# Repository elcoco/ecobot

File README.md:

# Ecobot :: A robot that draws stuff

Included in the repo are:

- CAD files created with [Freecad](https://www.freecadweb.org).
- PCB files created with [Kicad](https://www.kicad.org/).

Projects used:

- The [ESP32 port](https://github.com/bdring/Grbl_Esp32) of the great [GRBL](https://github.com/gnea/grbl) CNC controller firmware.
- [BCNC](https://github.com/vlachoudis/bCNC) command sender, autoleveler, g-code editor, digitizer, CAM and swiss army knife for all your CNC needs.

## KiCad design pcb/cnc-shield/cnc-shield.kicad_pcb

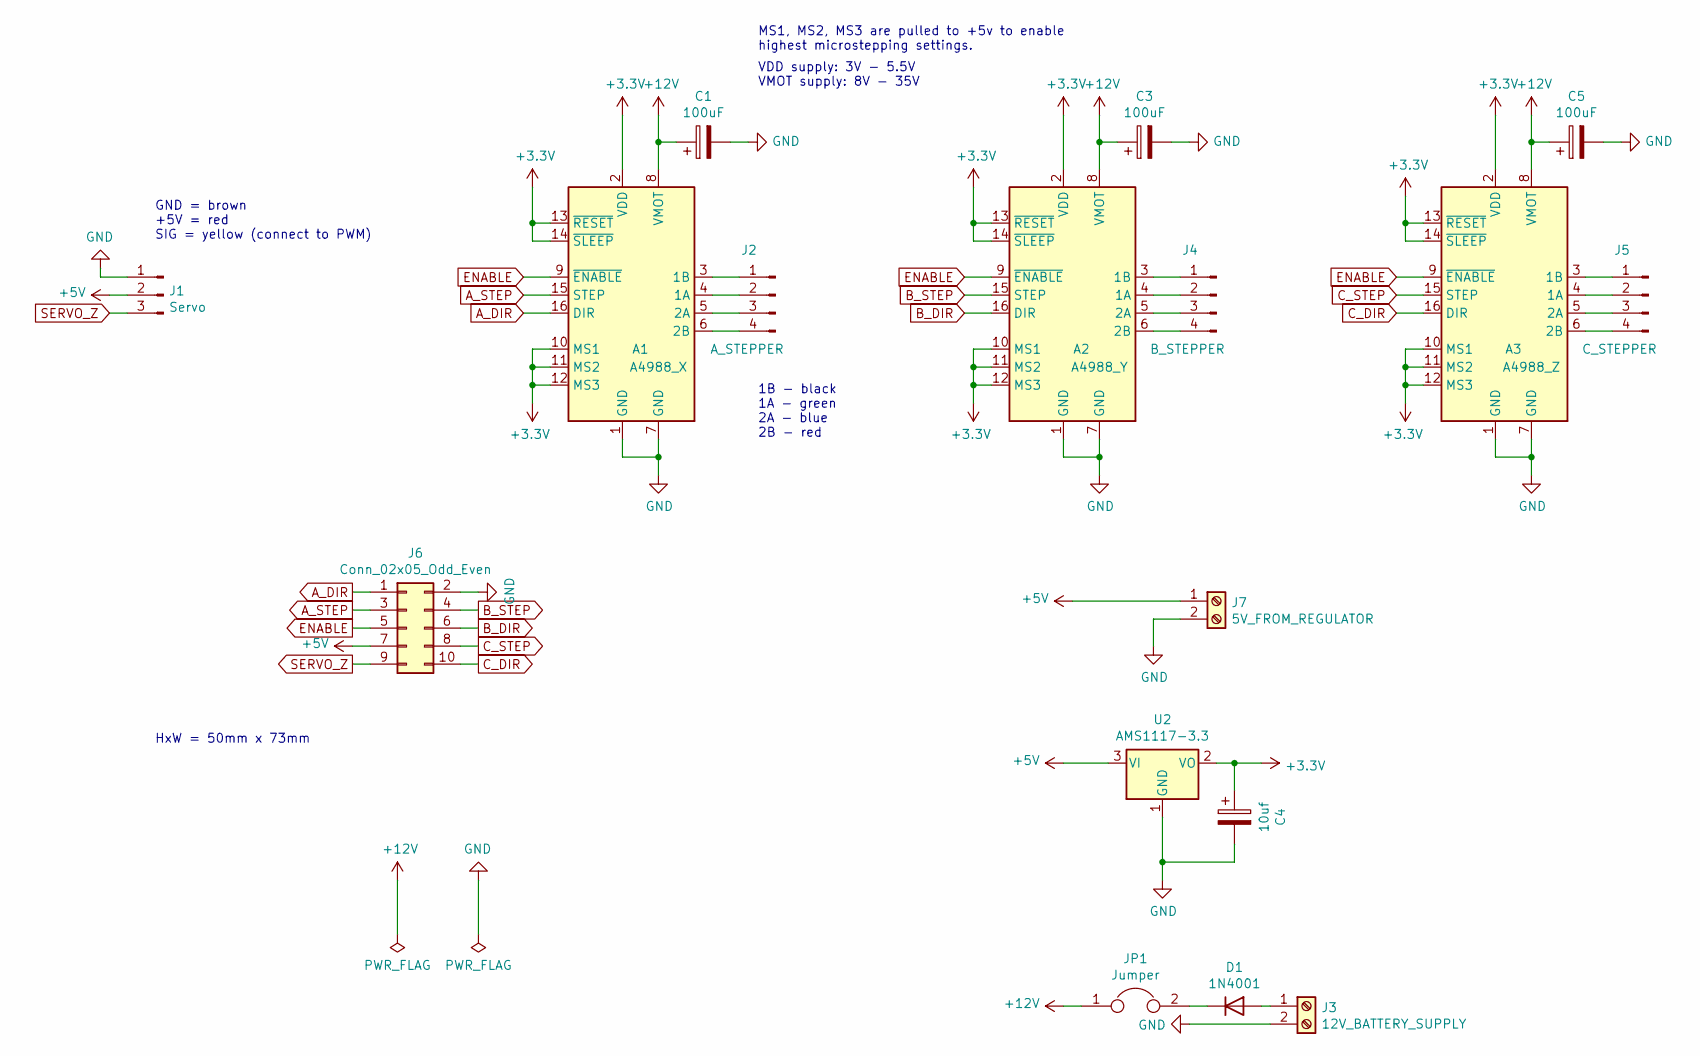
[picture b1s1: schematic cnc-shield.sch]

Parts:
A1: A4988_X; Pololu_Breakout-16_15.2x20.3mm
A2: A4988_Y; Pololu_Breakout-16_15.2x20.3mm
A3: A4988_Z; Pololu_Breakout-16_15.2x20.3mm
C1, C3, C5: 100uF; CP_Radial_D8.0mm_P3.80mm
C4: 10uf; CP_Radial_D8.0mm_P3.80mm
D1: 1N4001; D_DO-41_SOD81_P10.16mm_Horizontal
J1: Servo; PinHeader_1x03_P2.54mm_Vertical
J2: A_STEPPER; PinHeader_1x04_P2.54mm_Vertical
J3: 12V_BATTERY_SUPPLY; TerminalBlock_Phoenix_MKDS-1,5-2-5.08_1x02_P5.08mm_Horizont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
J4: B_STEPPER; PinHeader_1x04_P2.54mm_Vertical
J5: C_STEPPER; PinHeader_1x04_P2.54mm_Vertical
J6: Conn_02x05_Odd_Even; 2X5-SHROUDED_LOCK
J7: 5V_FROM_REGULATOR; TerminalBlock_Phoenix_MKDS-1,5-2-5.08_1x02_P5.08mm_Horizont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
JP1: Jumper; PinHeader_1x02_P2.54mm_Vertical
U2: AMS1117-3.3; SOT-223-3_TabPin2

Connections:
+3V3: A1.2 (VDD), A1.10 (MS1), A1.11 (MS2), A1.12 (MS3), A1.13 (~RESET), A1.14 (~SLEEP), A2.2 (VDD), A2.10 (MS1), A2.11 (MS2), A2.12 (MS3), A2.13 (~RESET), A2.14 (~SLEEP), A3.2 (VDD), A3.10 (MS1), A3.11 (MS2), A3.12 (MS3), A3.13 (~RESET), A3.14 (~SLEEP), C4.1, U2.2 (VO)
+5V: J1.2, J6.7, J7.1, U2.3 (VI)
+12V: A1.8 (VMOT), A2.8 (VMOT), A3.8 (VMOT), C1.1, C3.1, C5.1, JP1.1
A_DIR: A1.16 (DIR), J6.1
A_STEP: A1.15 (STEP), J6.3
B_DIR: A2.16 (DIR), J6.6
B_STEP: A2.15 (STEP), J6.4
C_DIR: A3.16 (DIR), J6.10
C_STEP: A3.15 (STEP), J6.8
ENABLE: A1.9 (~ENABLE), A2.9 (~ENABLE), A3.9 (~ENABLE), J6.5
GND: A1.1 (GND), A1.7 (GND), A2.1 (GND), A2.7 (GND), A3.1 (GND), A3.7 (GND), C1.2, C3.2, C4.2, C5.2, J1.1, J3.2, J6.2, J7.2, U2.1 (GND)
unnamed: A1.3 (1B), J2.1
unnamed: A1.4 (1A), J2.2
unnamed: A1.5 (2A), J2.3
unnamed: A1.6 (2B), J2.4
unnamed: A2.3 (1B), J4.1
unnamed: A2.4 (1A), J4.2
unnamed: A2.5 (2A), J4.3
unnamed: A2.6 (2B), J4.4
unnamed: A3.3 (1B), J5.1
unnamed: A3.4 (1A), J5.2
unnamed: A3.5 (2A), J5.3
unnamed: A3.6 (2B), J5.4
unnamed: D1.1 (K), JP1.2
unnamed: D1.2 (A), J3.1
SERVO_Z: J1.3, J6.9

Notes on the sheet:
MS1, MS2, MS3 are pulled to +5v to enable highest microstepping settings.
GND = brown +5V = red SIG = yellow (connect to PWM)
HxW = 50mm x 73mm
1B - black 1A - green 2A - blue 2B - red
VDD supply: 3V - 5.5V VMOT supply: 8V - 35V

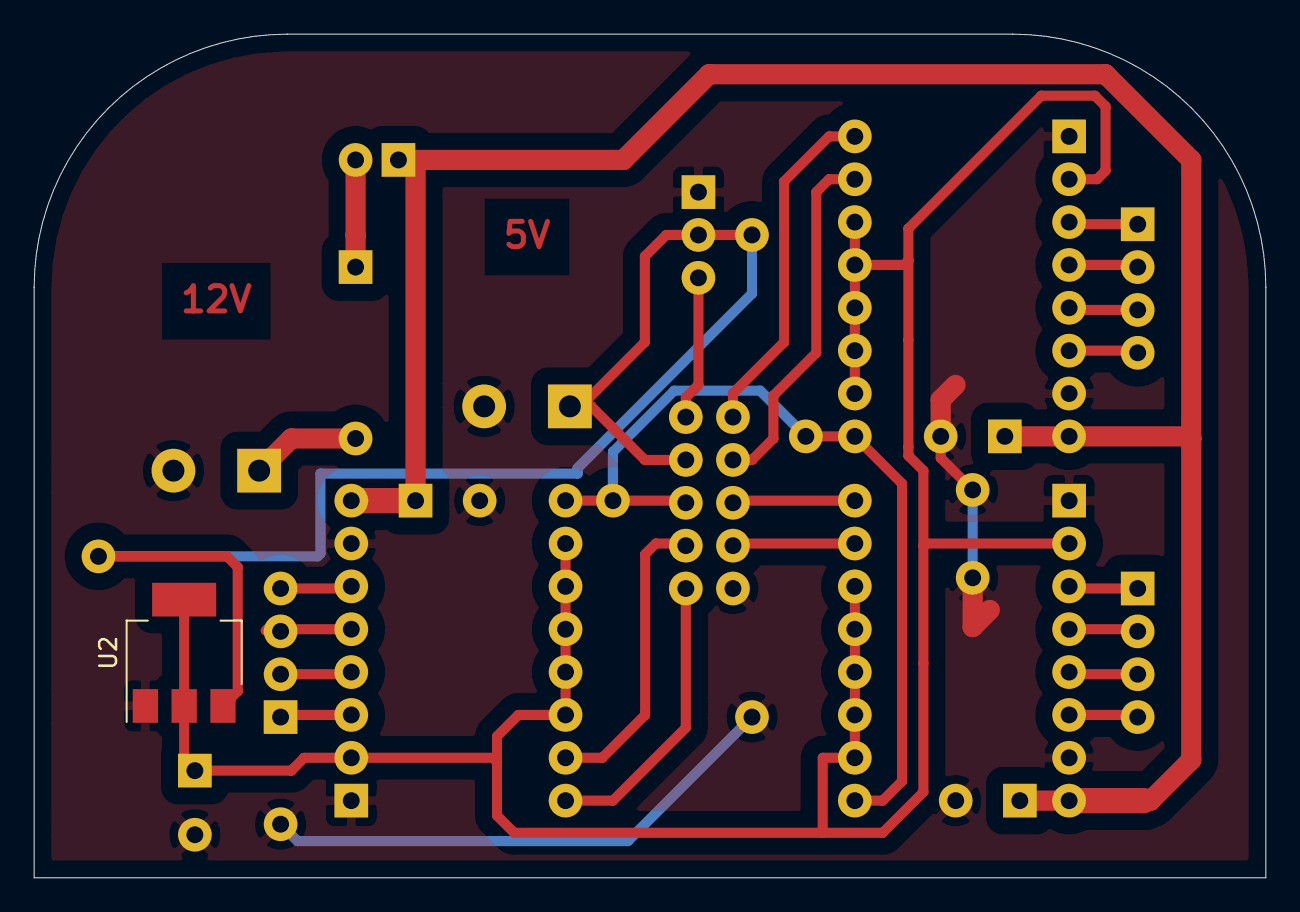
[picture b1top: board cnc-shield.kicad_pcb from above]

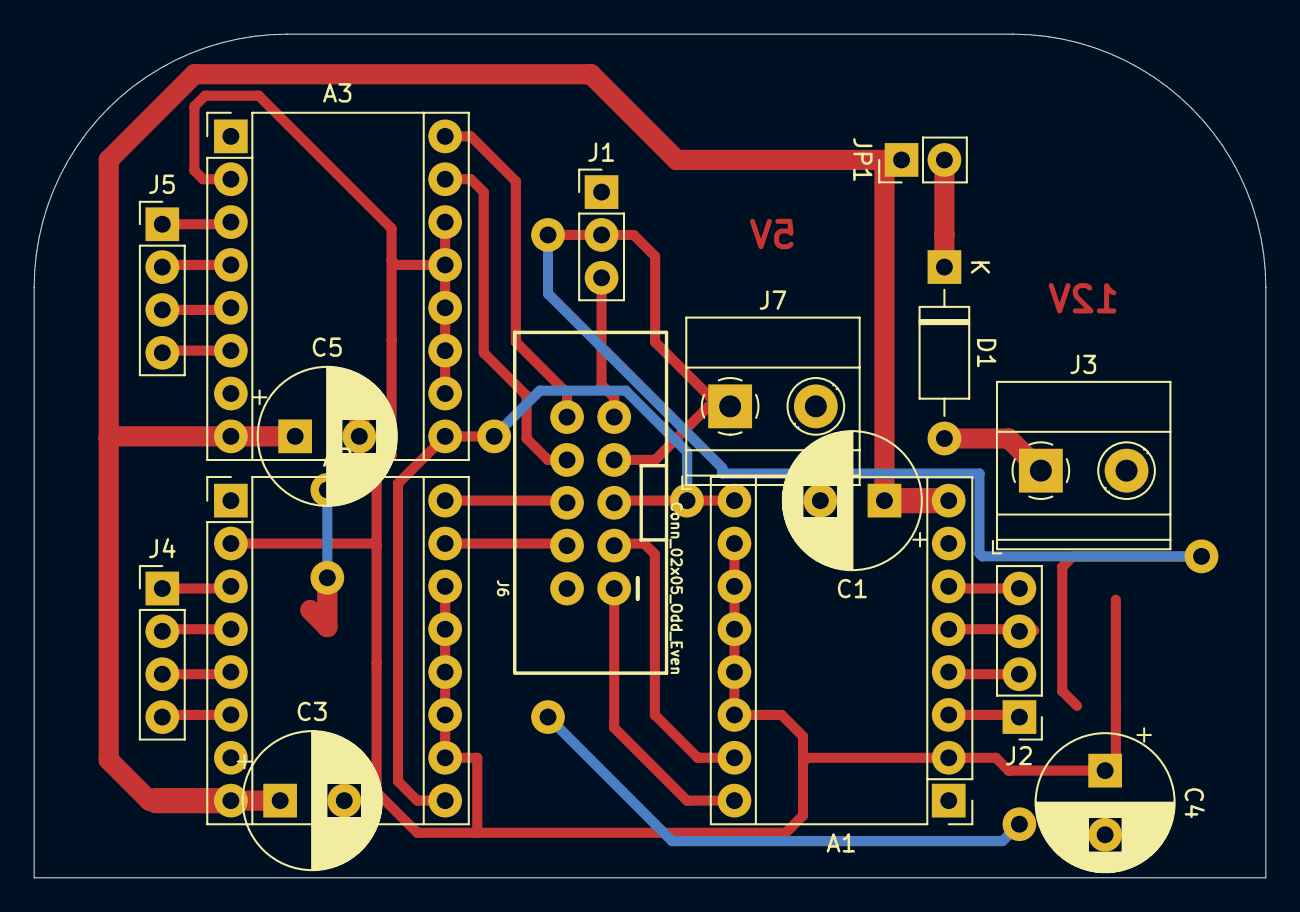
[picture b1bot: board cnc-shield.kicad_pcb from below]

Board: 2 copper layers, 73.0 x 50.0 mm, 17 parts (16 on the bottom side), 26 nets.

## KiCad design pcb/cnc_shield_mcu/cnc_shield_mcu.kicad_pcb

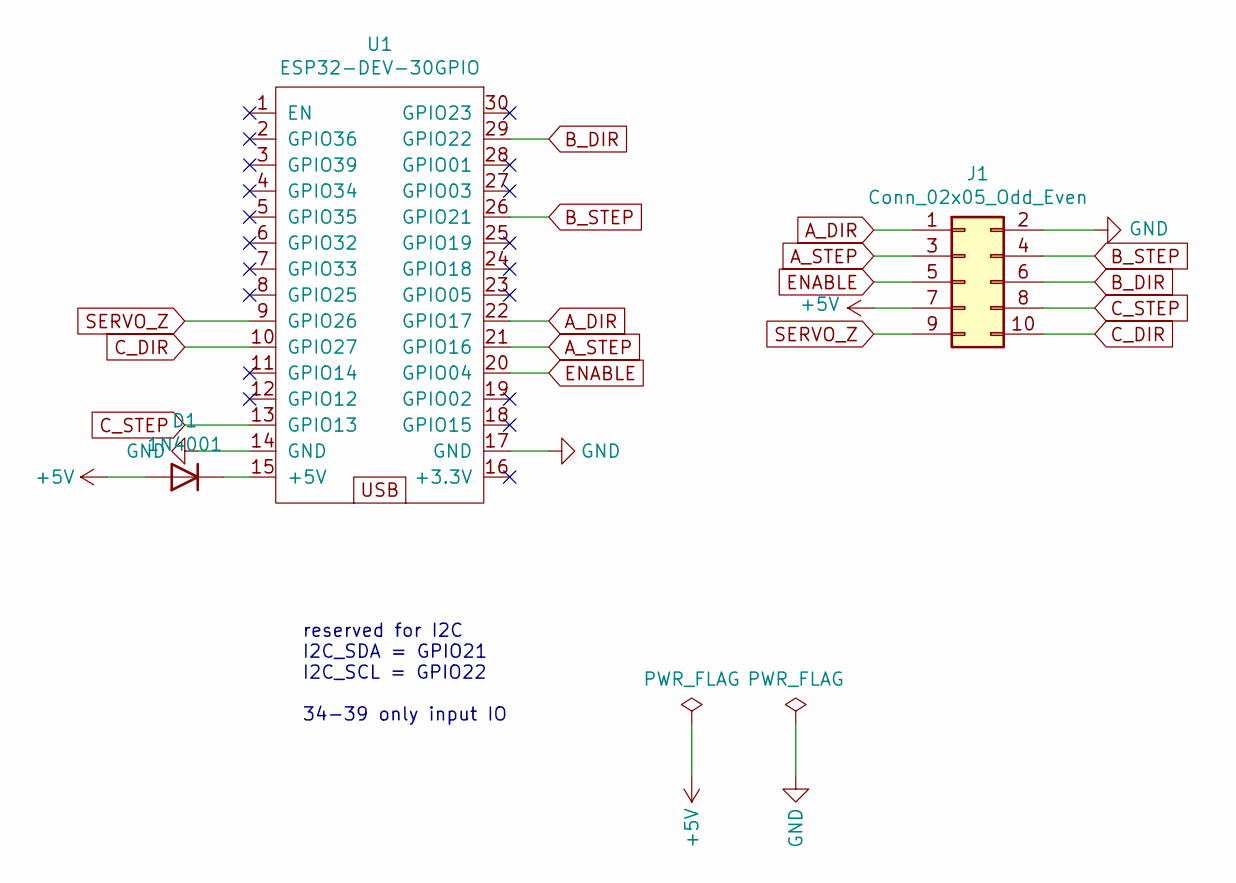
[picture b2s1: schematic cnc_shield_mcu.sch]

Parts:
D1: 1N4001; D_DO-41_SOD81_P10.16mm_Horizontal
J1: Conn_02x05_Odd_Even; 2X5-SHROUDED_LOCK
U1: ESP32-DEV-30GPIO; esp32_devkit_v1_doit

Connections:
+5V: D1.2 (A), J1.7
A_DIR: J1.1, U1.22 (GPIO17)
A_STEP: J1.3, U1.21 (GPIO16)
B_DIR: J1.6, U1.29 (GPIO22)
B_STEP: J1.4, U1.26 (GPIO21)
C_DIR: J1.10, U1.10 (GPIO27)
C_STEP: J1.8, U1.13 (GPIO13)
ENABLE: J1.5, U1.20 (GPIO04)
GND: J1.2, U1.14 (GND), U1.17 (GND)
unnamed: D1.1 (K), U1.15 (+5V)
SERVO_Z: J1.9, U1.9 (GPIO26)

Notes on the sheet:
reserved for I2C I2C_SDA = GPIO21 I2C_SCL = GPIO22 34-39 only input IO

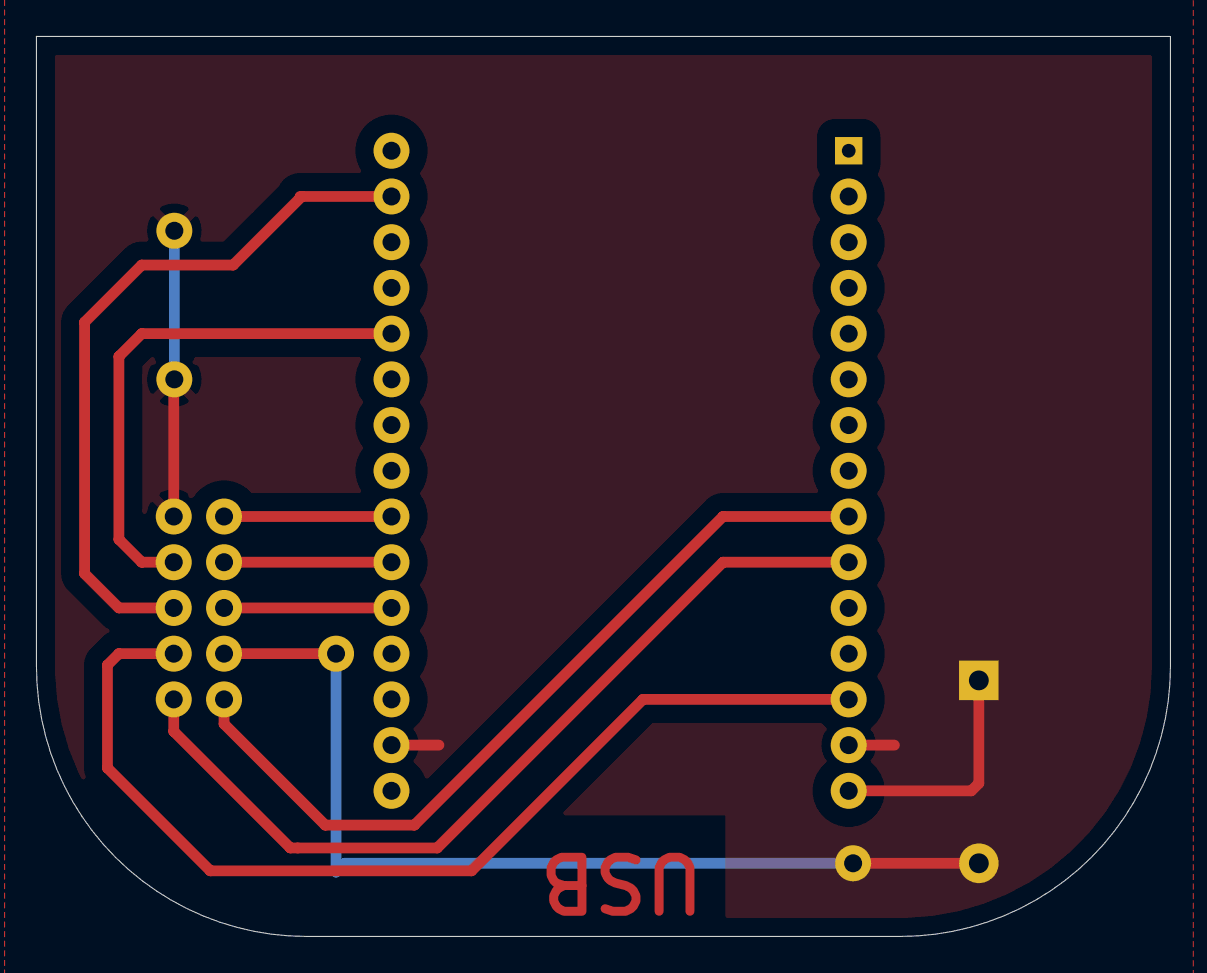
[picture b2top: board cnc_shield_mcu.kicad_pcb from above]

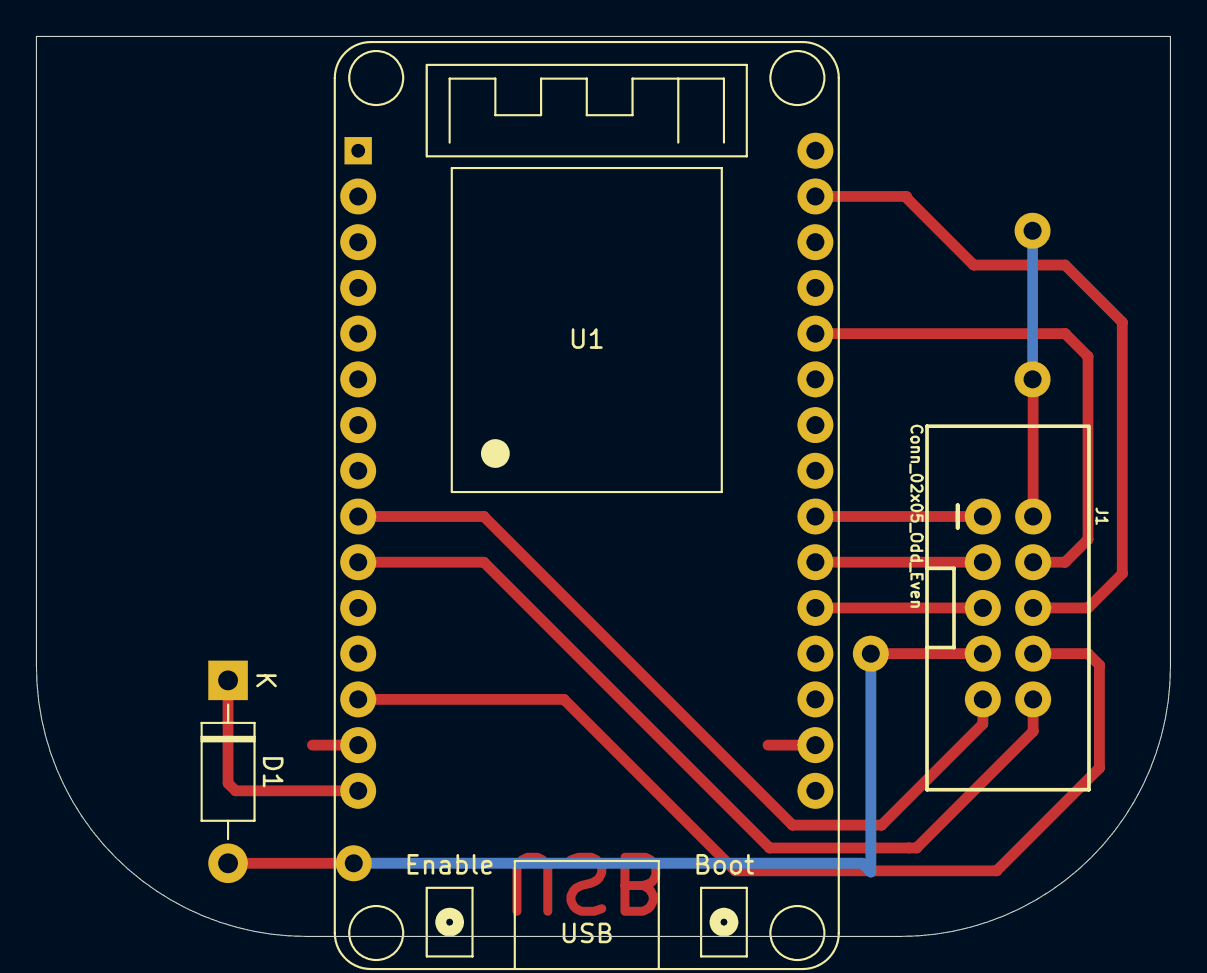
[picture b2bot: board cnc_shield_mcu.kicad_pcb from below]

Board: 2 copper layers, 63.0 x 50.0 mm, 3 parts (3 on the bottom side), 11 nets.

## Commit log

2022-01-28 move to github
2022-01-28 readme
2022-01-28 added some pics
2022-01-28 moved parts.ods
